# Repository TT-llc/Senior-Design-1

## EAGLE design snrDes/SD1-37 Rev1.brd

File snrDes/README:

File contains all board files for control board including revs and CAM

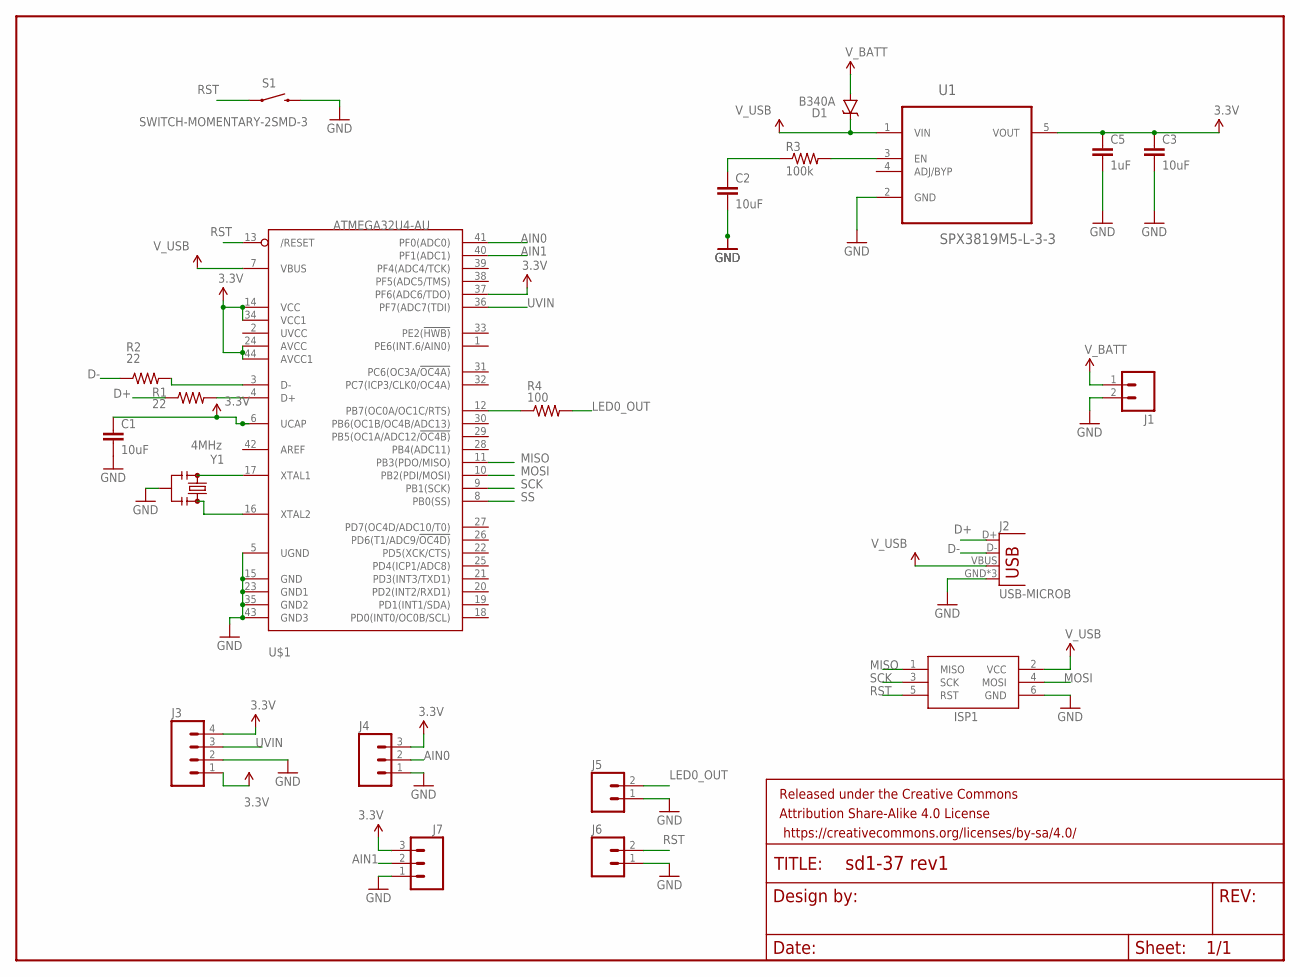
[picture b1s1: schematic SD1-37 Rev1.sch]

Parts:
C1, C2, C3: 10uF; 0805
C5: 1uF; 0805
D1: B340A; SMA-DIODE
FRAME1: FRAME-LETTER; CREATIVE_COMMONS
ISP1: AVRISP-6; AVRISP
J1: M02PTH; 1X02
J2: USB-MICROB
J3: M04SCREW; SCREWTERMINAL-3.5MM-4
J4, J7: M03SCREW; SCREWTERMINAL-3.5MM-3
J5, J6: M023.5MM; SCREWTERMINAL-3.5MM-2
R1, R2: 22; 0805
R3: 100k; 0805
R4: 100; 0805
S1: SWITCH-MOMENTARY-2SMD-3; TACTILE_SWITCH_SMD-3
U1: SPX3819M5-L-3-3; SOT95P280X145-5N
U$1: ATMEGA32U4-AU; TQFP44
Y1: 4MHz; RESONATOR-SMD_MED

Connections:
3.3V: C1.1, C3.1, C5.1, J3.1, J3.4, J4.3, J7.3, U1.5 (VOUT), U$1.6 (UCAP), U$1.14 (VCC), U$1.24 (AVCC), U$1.34 (VCC1), U$1.37 (PF6(ADC6/TDO)), U$1.44 (AVCC1)
AIN0: J4.2, U$1.41 (PF0(ADC0))
AIN1: J7.2, U$1.40 (PF1(ADC1))
D+: J2.D+, R1.1
D-: J2.D-, R2.1
GND: C1.2, C2.2, C3.2, C5.2, ISP1.6 (GND), J1.2, J2.GND, J2.MT1 (GND), J2.MT2 (GND), J3.2, J4.1, J5.1, J6.1, J7.1, S1.4 (2), U1.2 (GND), U$1.5 (UGND), U$1.15 (GND), U$1.23 (GND1), U$1.35 (GND2), U$1.43 (GND3), Y1.2
LED0_OUT: J5.2, R4.2
MISO: ISP1.1 (MISO), U$1.11 (PB3(PDO/MISO))
MOSI: ISP1.4 (MOSI), U$1.10 (PB2(PDI/MOSI))
unnamed: R1.2, U$1.4 (D+)
unnamed: U$1.17 (XTAL1), Y1.1
unnamed: U$1.16 (XTAL2), Y1.3
unnamed: R2.2, U$1.3 (D-)
unnamed: R4.1, U$1.12 (PB7(OC0A/OC1C/RTS))
unnamed: R3.2, U1.3 (EN)
unnamed: C2.1, R3.1
RST: ISP1.5 (RST), J6.2, S1.1, U$1.13 (/RESET)
SCK: ISP1.3 (SCK), U$1.9 (PB1(SCK))
SS: U$1.8 (PB0(SS))
UVIN: J3.3, U$1.36 (PF7(ADC7(TDI))
V_BATT: D1.A, J1.1
V_USB: D1.C, ISP1.2 (VCC), J2.VBUS, U1.1 (VIN), U$1.7 (VBUS)

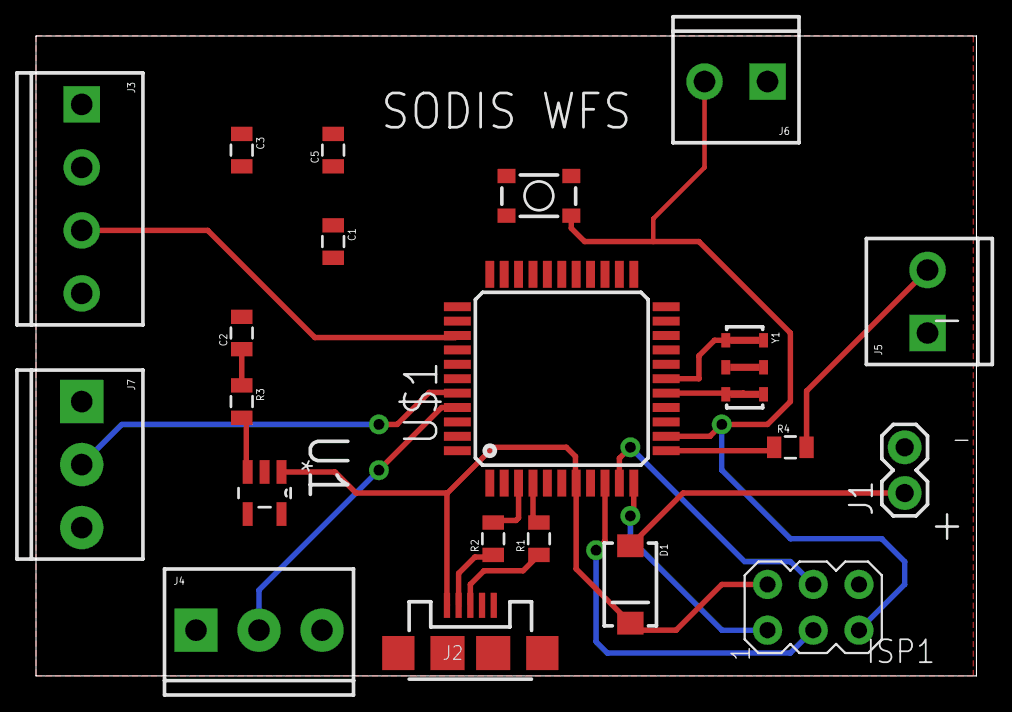
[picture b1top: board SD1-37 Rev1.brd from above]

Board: 2 copper layers, 52.2 x 35.5 mm, 22 parts (0 on the bottom side), 21 nets.

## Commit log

2016-09-28 :octocat: Added .gitattributes & .gitignore files
2016-10-14 Create boardFiles

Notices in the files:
parts and their libraries:
SparkFun-Capacitors: Licensing: Creative Commons ShareAlike 4.0 International - https://creativecommons.org/licenses/by-sa/4.0
SparkFun-Aesthetics: Released under the Creative Commons Attribution Share-Alike 4.0 License
SparkFun-Aesthetics: https://creativecommons.org/licenses/by-sa/4.0
